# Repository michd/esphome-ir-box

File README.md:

# ESPHome IR Box

A device mainly intended to tie A/C units that are controlled by infrared remote control into Home Assistant, by running esphome on it and having an IR LED and receiver.

It can also control other IR devices within line of sight, of course; TVs, remote controlled RGB LED bulbs come to mind.

This project is derived from one where I use an identical esp32 dev board as a WLED controller. This has different supporting hardware, though.

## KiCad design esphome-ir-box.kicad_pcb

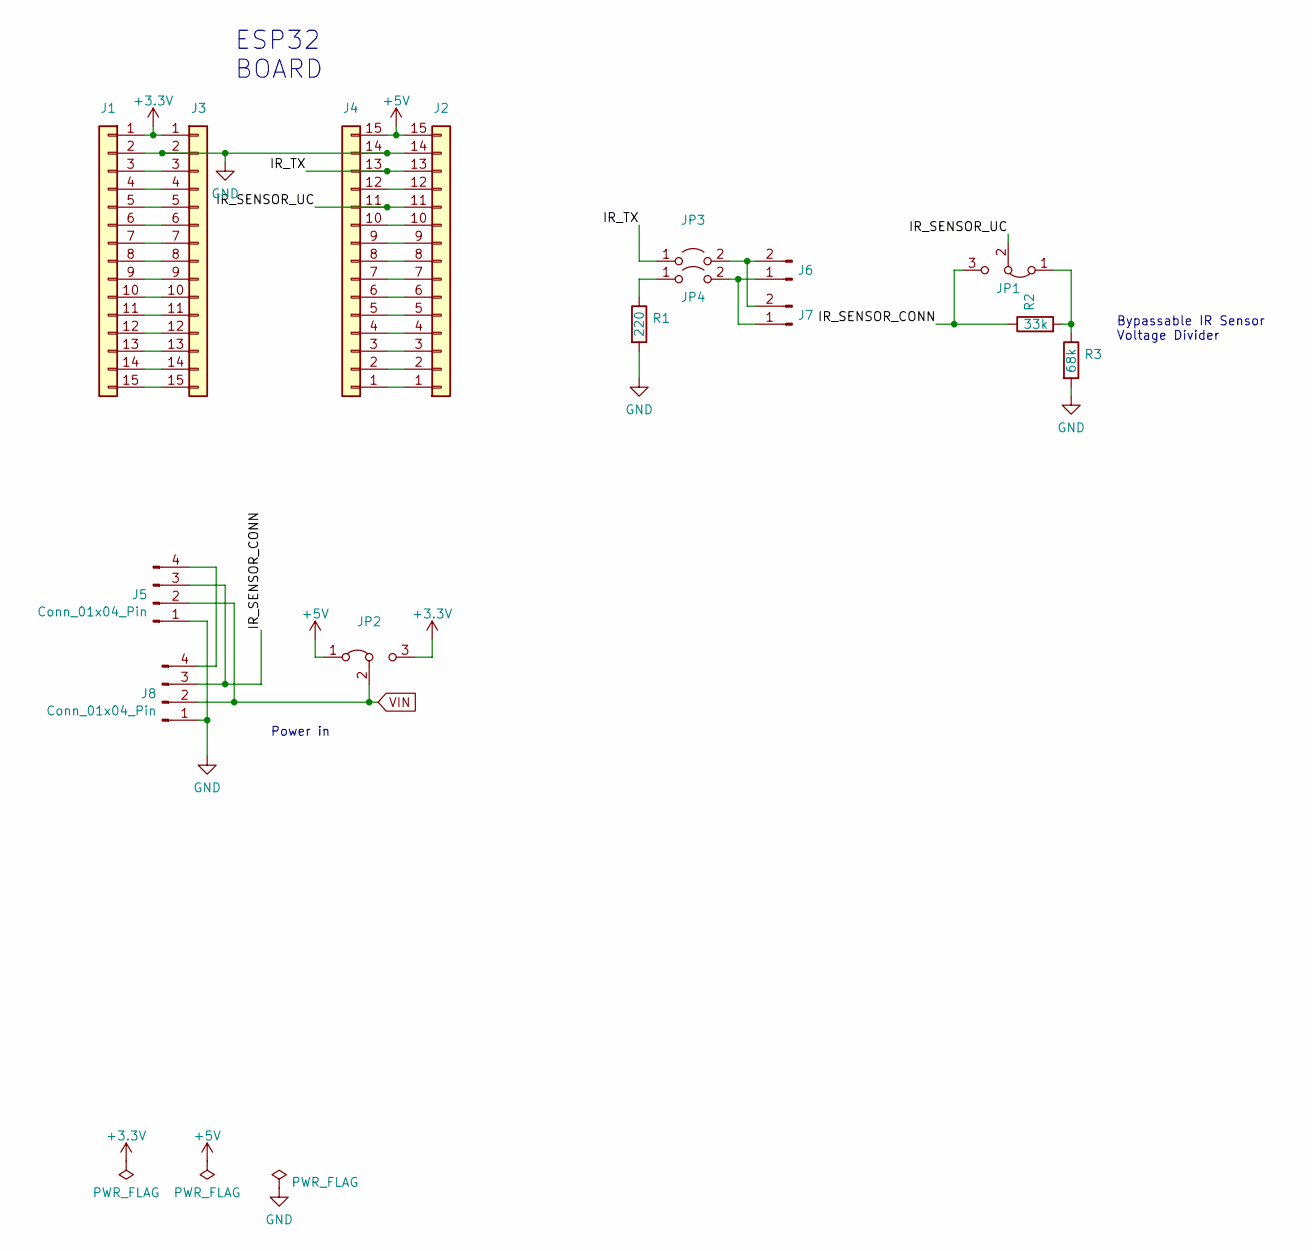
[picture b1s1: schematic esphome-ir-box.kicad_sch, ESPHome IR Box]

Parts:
J1, J2: Conn_01x15_Female; PinSocket_1x15_P2.54mm_Vertical
J3, J4: Conn_01x15_Male; PinHeader_1x15_P2.54mm_Vertical
J5: Conn_01x04_Pin; PinHeader_1x04_P2.54mm_Vertical
J6: Conn_01x02_Pin; JST_PH_S2B-PH-K_1x02_P2.00mm_Horizontal
J7: Conn_01x02_Pin; PinHeader_1x02_P2.54mm_Vertical
J8: Conn_01x04_Pin; JST_PH_S4B-PH-K_1x04_P2.00mm_Horizontal
JP1, JP2: Jumper_3_Bridged12; SolderJumper-3_P2.0mm_Open_TrianglePad1.0x1.5mm
JP3, JP4: Jumper_2_Open; SolderJumper-2_P1.3mm_Open_TrianglePad1.0x1.5mm
R1: 220; R_0603_1608Metric; LCSC C22962
R2: 33k; R_0603_1608Metric; LCSC C4216
R3: 68k; R_0603_1608Metric; LCSC C23231

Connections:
+3.3V: J1.1, J3.1, JP2.3 (B)
+5V: J2.15, J4.15, JP2.1 (A)
/IR_SENSOR_CONN: J5.3, J8.3, JP1.3 (B), R2.1
/IR_SENSOR_UC: J2.11, J4.11, JP1.2 (C)
/IR_TX: J2.13, J4.13, JP3.1 (A)
GND: J1.2, J2.14, J3.2, J4.14, J5.1, J8.1, R1.2, R3.2
unnamed: J1.3, J3.3
unnamed: J1.4, J3.4
unnamed: J1.5, J3.5
unnamed: J1.6, J3.6
unnamed: J1.7, J3.7
unnamed: J1.8, J3.8
unnamed: J1.9, J3.9
unnamed: J1.10, J3.10
unnamed: J1.11, J3.11
unnamed: J1.12, J3.12
unnamed: J1.13, J3.13
unnamed: J1.14, J3.14
unnamed: J1.15, J3.15
unnamed: J2.1, J4.1
unnamed: J2.2, J4.2
unnamed: J2.3, J4.3
unnamed: J2.4, J4.4
unnamed: J2.5, J4.5
unnamed: J2.6, J4.6
unnamed: J2.7, J4.7
unnamed: J2.8, J4.8
unnamed: J2.9, J4.9
unnamed: J2.10, J4.10
unnamed: J2.12, J4.12
unnamed: J5.4, J8.4
unnamed: J6.1, J7.1, JP4.2 (B)
unnamed: J6.2, J7.2, JP3.2 (B)
unnamed: JP1.1 (A), R2.2, R3.1
unnamed: JP4.1 (A), R1.1
VIN: J5.2, J8.2, JP2.2 (C)

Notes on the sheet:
Power in
Bypassable IR Sensor Voltage Divider
ESP32 BOARD

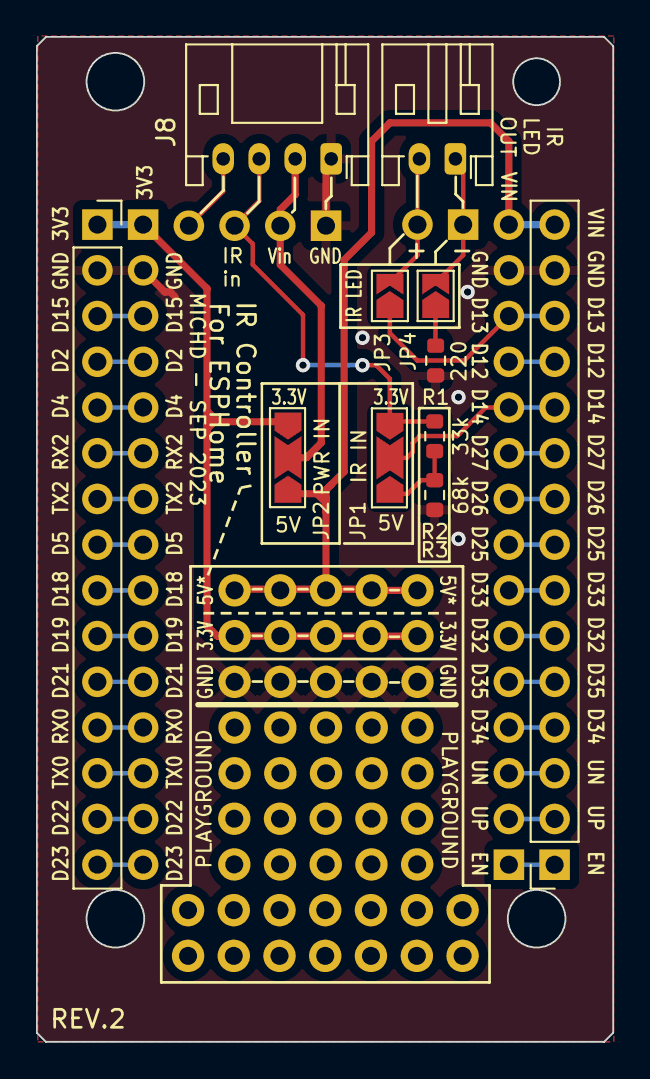
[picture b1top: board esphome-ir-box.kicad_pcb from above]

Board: 2 copper layers, 32.0 x 55.8 mm, 15 parts (0 on the bottom side), 36 nets.

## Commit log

2023-02-11 Initial commit: rev0
2023-03-19 Fix VS1813B pinout, KiCad 7 tweaks
2023-09-30 Ignore kicad lock files
2023-09-30 Revise board, focussing on building into devices
    New board layout has very few onboard components, and focuses on wiring
    an IR LED into an existing device (next to its sensor), while leeching
    power of the host device and piggybacking off its IR sensor.
    There are jumpers for selecting input voltage (5V or 3.3V) which
    determines where power gets routed to on the esp32 dev board, as well as
    a bypassable voltage divider for the IR input. So if the host device
2023-10-05 Add JLC mfr order no placeholder
